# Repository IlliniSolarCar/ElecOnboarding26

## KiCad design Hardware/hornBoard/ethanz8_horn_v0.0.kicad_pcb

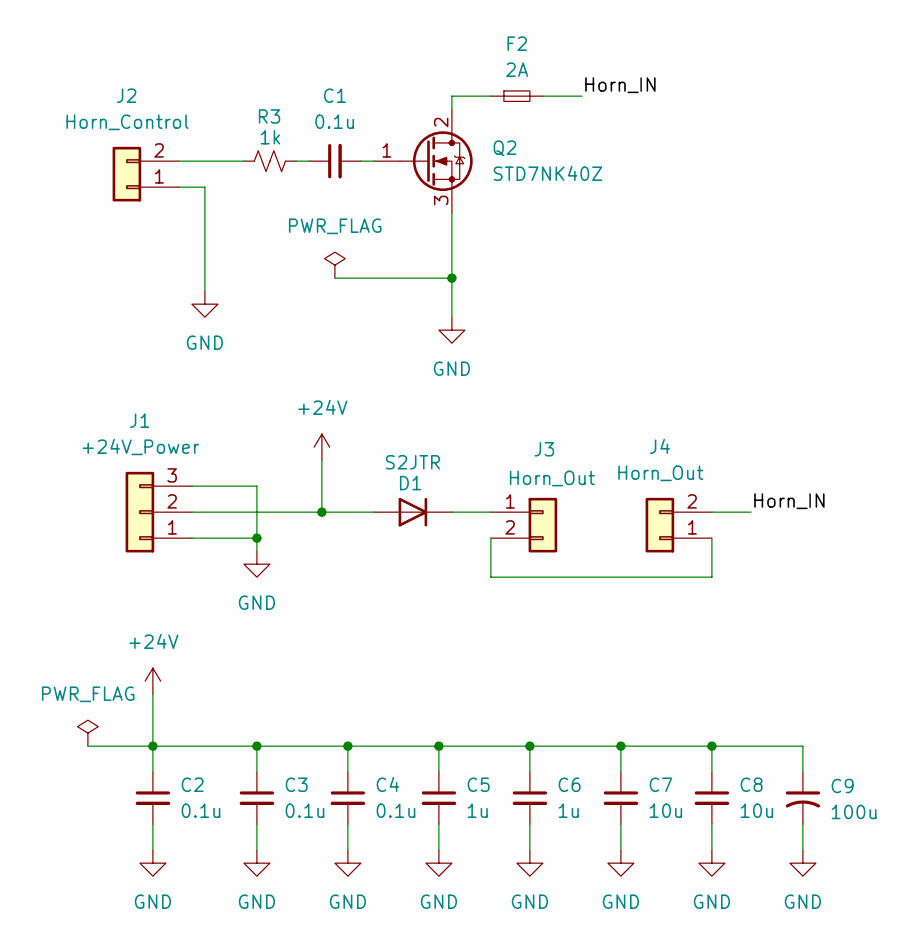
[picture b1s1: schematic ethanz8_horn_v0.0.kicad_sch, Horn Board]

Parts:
C1, C2, C3, C4: 0.1u; C_0402_1005Metric_Pad0.74x0.62mm_HandSolder
C5, C6: 1u; C_0603_1608Metric_Pad1.08x0.95mm_HandSolder
C7, C8: 10u; CP_Elec_4x5.4
C9: 100u; CP_Elec_8x10
D1: S2JTR; D_SMB
F2: 2A; Fuse_0402_1005Metric_Pad0.77x0.64mm_HandSolder
J1: +24V_Power; Molex_KK-254_AE-6410-03A_1x03_P2.54mm_Vertical
J2: Horn_Control; Molex_KK-254_AE-6410-02A_1x02_P2.54mm_Vertical
J3, J4: Horn_Out; Molex_KK-254_AE-6410-02A_1x02_P2.54mm_Vertical
Q2: STD7NK40Z; TO-252-2
R3: 1k; R_0603_1608Metric_Pad0.98x0.95mm_HandSolder

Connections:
+24V: C2.1, C3.1, C4.1, C5.1, C6.1, C7.1, C8.1, C9.1, D1.2 (A), J1.2
/Horn_IN: F2.2, J4.2
GND: C2.2, C3.2, C4.2, C5.2, C6.2, C7.2, C8.2, C9.2, J1.1, J1.3, J2.1, Q2.3 (S)
unnamed: C1.1, R3.2
unnamed: D1.1 (K), J3.1
unnamed: J2.2, R3.1
unnamed: J3.2, J4.1
unnamed: F2.1, Q2.2 (D)
unnamed: C1.2, Q2.1 (G)

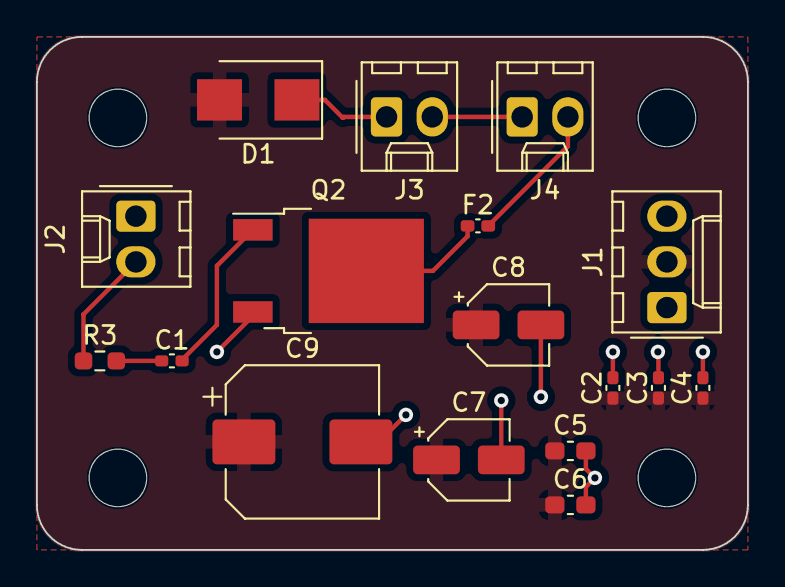
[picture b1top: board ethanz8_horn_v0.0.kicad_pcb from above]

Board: 2 copper layers, 39.5 x 28.5 mm, 17 parts (0 on the bottom side), 9 nets.

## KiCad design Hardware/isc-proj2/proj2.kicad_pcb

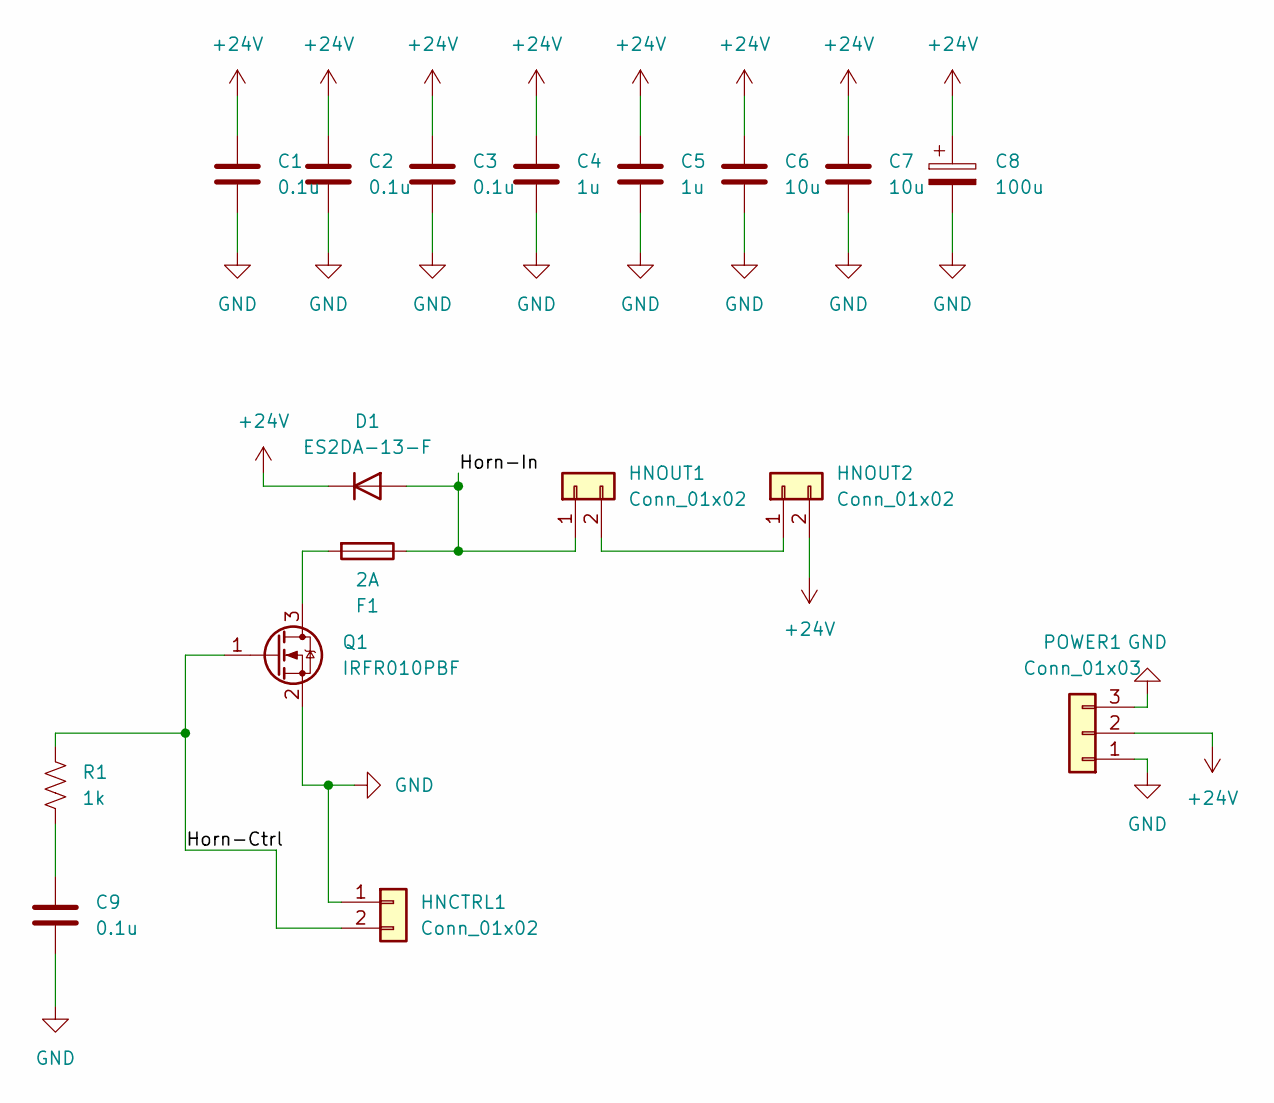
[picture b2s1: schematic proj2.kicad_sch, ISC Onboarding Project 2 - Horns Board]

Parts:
C1, C2, C3, C9: 0.1u; C_0402_1005Metric_Pad0.74x0.62mm_HandSolder
C4, C5: 1u; C_0402_1005Metric_Pad0.74x0.62mm_HandSolder
C6, C7: 10u; C_0402_1005Metric_Pad0.74x0.62mm_HandSolder
C8: 100u; C_0402_1005Metric_Pad0.74x0.62mm_HandSolder
D1: ES2DA-13-F; D_3220_8050Metric_Pad2.65x5.15mm_HandSolder
F1: 2A; Fuse_0402_1005Metric_Pad0.77x0.64mm_HandSolder
HNCTRL1: Conn_01x02; Molex_KK-254_AE-6410-02A_1x02_P2.54mm_Vertical
HNOUT1, HNOUT2: Conn_01x02; Molex_KK-254_AE-6410-02A_1x02_P2.54mm_Vertical
POWER1: Conn_01x03; Molex_KK-254_AE-6410-03A_1x03_P2.54mm_Vertical
Q1: IRFR010PBF; SOT-23
R1: 1k; R_0603_1608Metric_Pad0.98x0.95mm_HandSolder

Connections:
+24V: C1.1, C2.1, C3.1, C4.1, C5.1, C6.1, C7.1, C8.1, D1.1 (K), HNOUT2.2, POWER1.2
/Horn-Ctrl: HNCTRL1.2, Q1.1 (G), R1.1
/Horn-In: D1.2 (A), F1.1, HNOUT1.1
GND: C1.2, C2.2, C3.2, C4.2, C5.2, C6.2, C7.2, C8.2, C9.2, HNCTRL1.1, POWER1.1, POWER1.3, Q1.2 (S)
unnamed: C9.1, R1.2
unnamed: HNOUT1.2, HNOUT2.1
unnamed: F1.2, Q1.3 (D)

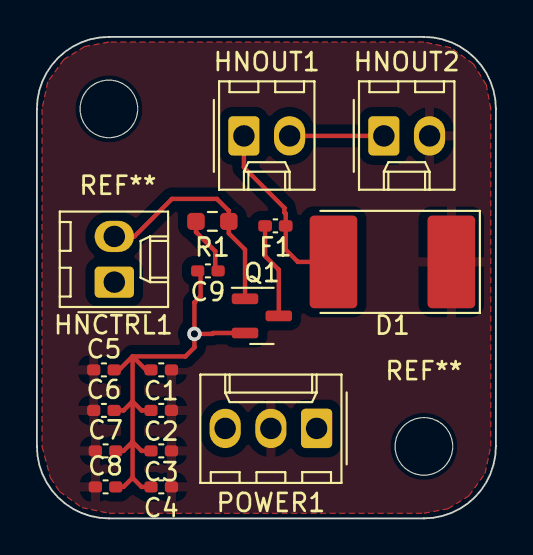
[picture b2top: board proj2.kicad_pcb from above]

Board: 2 copper layers, 25.5 x 26.8 mm, 17 parts (0 on the bottom side), 7 nets.

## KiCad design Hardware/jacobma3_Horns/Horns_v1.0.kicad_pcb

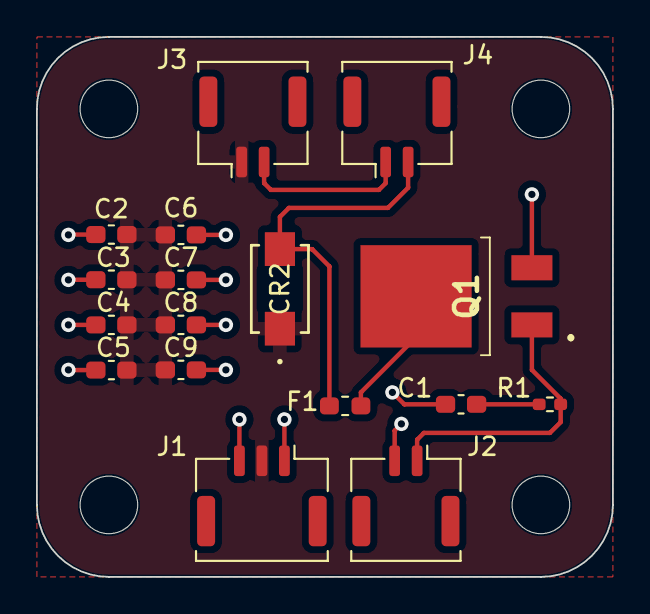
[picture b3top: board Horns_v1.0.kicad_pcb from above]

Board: 2 copper layers, 32.0 x 30.0 mm, 17 parts (0 on the bottom side), 7 nets.

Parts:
C1, C2, C3, C4: .1μF; C_0603_1608Metric_Pad1.08x0.95mm_HandSolder
C5, C6: 1μF; C_0603_1608Metric_Pad1.08x0.95mm_HandSolder
C7, C8: 10μF; C_0603_1608Metric_Pad1.08x0.95mm_HandSolder
C9: 100μF; C_0603_1608Metric_Pad1.08x0.95mm_HandSolder
CR2: ES2DA-13-F; CR_SMA_DIO
F1: 2A; Fuse_0603_1608Metric_Pad1.05x0.95mm_HandSolder
J1: Conn_01x03; Molex_CLIK-Mate_502382-0370_1x03-1MP_P1.25mm_Vertical
J2, J3, J4: Conn_01x02; Molex_CLIK-Mate_502382-0270_1x02-1MP_P1.25mm_Vertical
Q1: IRFR010PBF-BE3; SQD30N0520L_GE3
R1: 1k; R_0402_1005Metric_Pad0.72x0.64mm_HandSolder

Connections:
+24V: C2.2, C3.2, C4.2, C5.2, C6.2, C7.2, C8.2, C9.1, CR2.1, J1.2, J3.1
/HORN_CTRL: J2.1, Q1.1 (G), R1.2
/HORN_IN: CR2.2, F1.2, J4.2
GND: C1.1, C2.1, C3.1, C4.1, C5.1, C6.1, C7.1, C8.1, C9.2, J1.1, J1.3, J2.2, Q1.3 (S)
unnamed: C1.2, R1.1
unnamed: J3.2, J4.1
unnamed: F1.1, Q1.2 (D)

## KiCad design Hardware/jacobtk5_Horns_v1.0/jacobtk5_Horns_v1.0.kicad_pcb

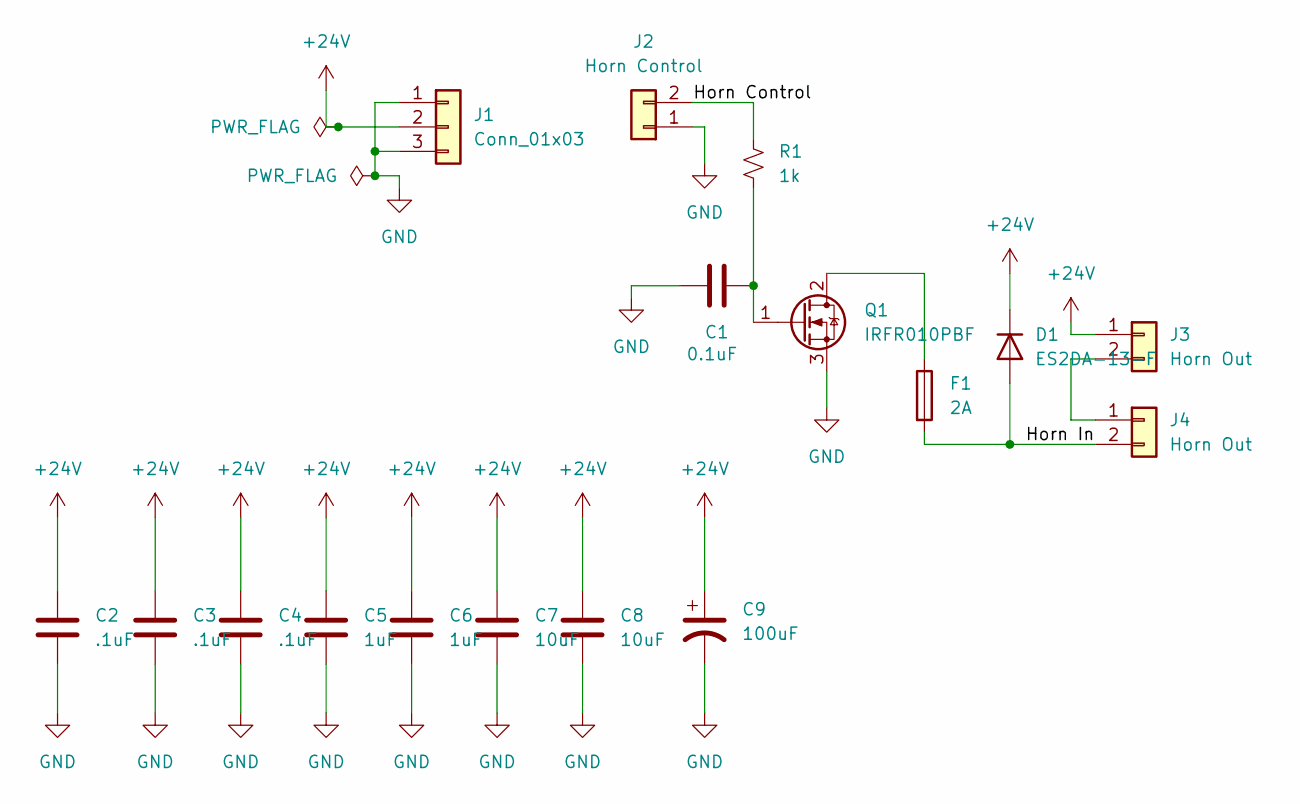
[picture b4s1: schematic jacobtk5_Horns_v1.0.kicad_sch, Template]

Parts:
C1: 0.1uF; CP_Elec_3x5.3
C2, C3, C4: .1uF; CP_Elec_3x5.3
C5, C6: 1uF; CP_Elec_3x5.3
C7, C8: 10uF; CP_Elec_3x5.3
C9: 100uF; CP_Elec_3x5.3
D1: ES2DA-13-F; D_SMB
F1: 2A; Fuse_0402_1005Metric
J1: Conn_01x03; Molex_KK-254_AE-6410-03A_1x03_P2.54mm_Vertical
J2: Horn Control; Molex_KK-254_AE-6410-02A_1x02_P2.54mm_Vertical
J3, J4: Horn Out; Molex_KK-254_AE-6410-02A_1x02_P2.54mm_Vertical
Q1: IRFR010PBF; TO-252-3_TabPin2
R1: 1k; R_0603_1608Metric_Pad0.98x0.95mm_HandSolder

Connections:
+24V: C2.1, C3.1, C4.1, C5.1, C6.1, C7.1, C8.1, C9.1, D1.1 (K), J1.2, J3.1
/Horn Control: J2.2, R1.1
/Horn In: D1.2 (A), F1.2, J4.2
GND: C1.2, C2.2, C3.2, C4.2, C5.2, C6.2, C7.2, C8.2, C9.2, J1.1, J1.3, J2.1, Q1.3 (S)
unnamed: J3.2, J4.1
unnamed: F1.1, Q1.2 (D)
unnamed: C1.1, Q1.1 (G), R1.2

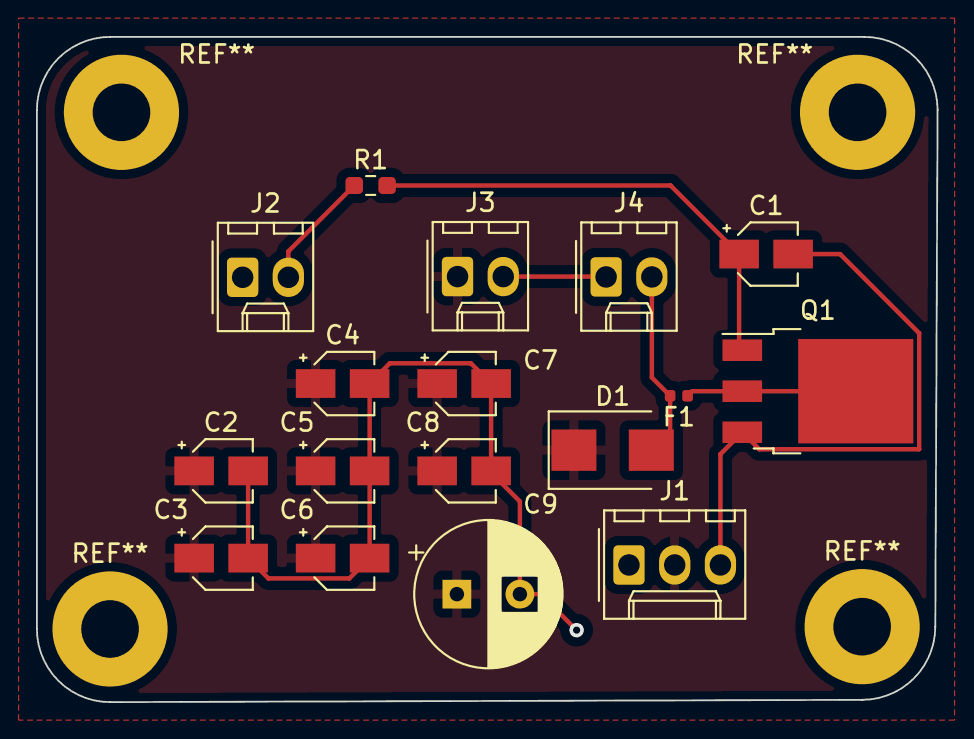
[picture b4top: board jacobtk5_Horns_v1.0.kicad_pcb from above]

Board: 2 copper layers, 50.0 x 37.0 mm, 17 parts (0 on the bottom side), 7 nets.

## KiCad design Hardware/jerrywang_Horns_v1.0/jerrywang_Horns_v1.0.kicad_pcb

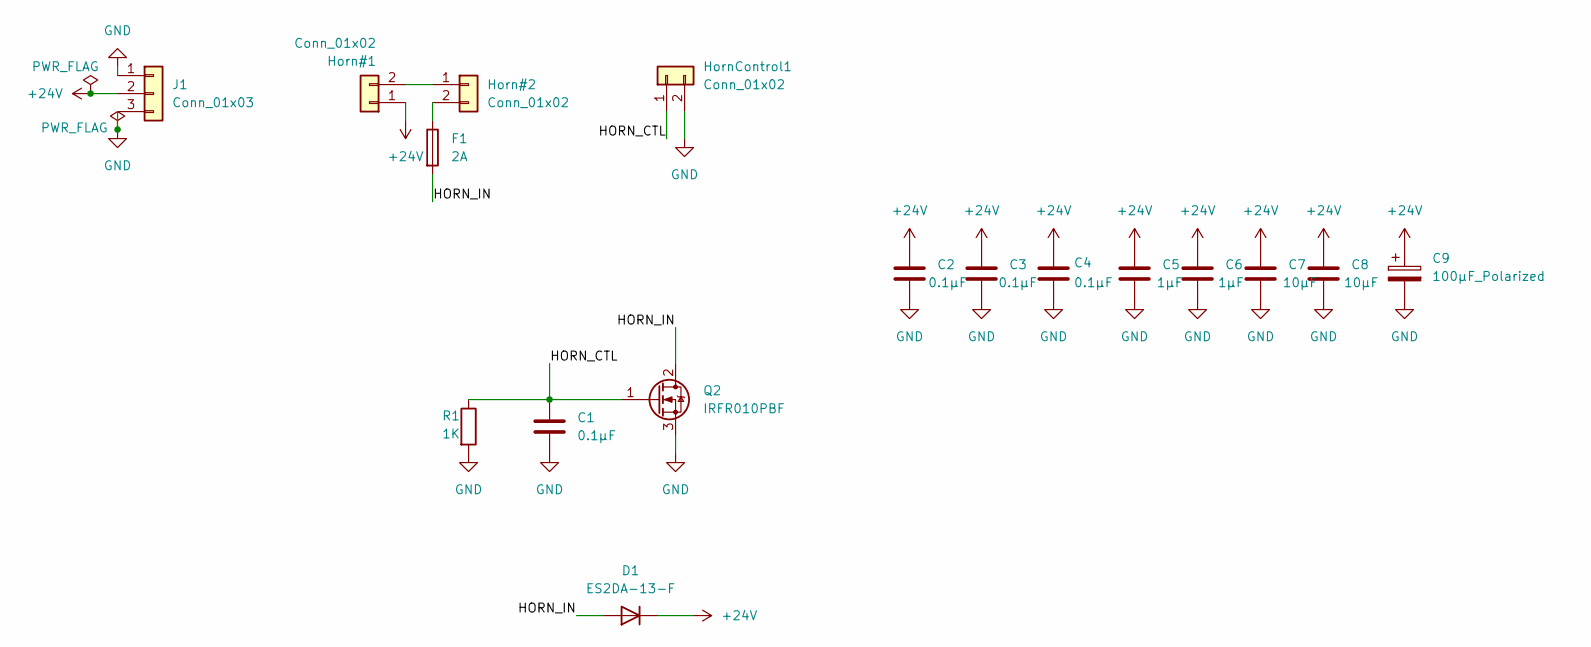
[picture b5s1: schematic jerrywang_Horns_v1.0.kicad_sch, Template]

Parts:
C1, C2, C3, C4: 0.1µF; C_1206_3216Metric
C5, C6: 1µF; C_1206_3216Metric
C7, C8: 10µF; C_1206_3216Metric
C9: 100µF_Polarized; CP_Radial_D8.0mm_P3.50mm
D1: ES2DA-13-F; D_SMA
F1: 2A; Fuse_1206_3216Metric
Horn#1, Horn#2: Conn_01x02; PinSocket_1x02_P2.54mm_Vertical
HornControl1: Conn_01x02; PinSocket_1x02_P2.54mm_Vertical
J1: Conn_01x03; PinSocket_1x03_P2.54mm_Vertical
Q2: IRFR010PBF; TO-252-2
R1: 1K; R_1206_3216Metric

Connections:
+24V: C2.1, C3.1, C4.1, C5.1, C6.1, C7.1, C8.1, C9.1, D1.1 (K), Horn#1.1, J1.2
/HORN_CTL: C1.1, HornControl1.1, Q2.1 (G), R1.1
/HORN_IN: D1.2 (A), F1.2, Q2.2 (D)
GND: C1.2, C2.2, C3.2, C4.2, C5.2, C6.2, C7.2, C8.2, C9.2, HornControl1.2, J1.1, J1.3, Q2.3 (S), R1.2
unnamed: Horn#1.2, Horn#2.1
unnamed: F1.1, Horn#2.2

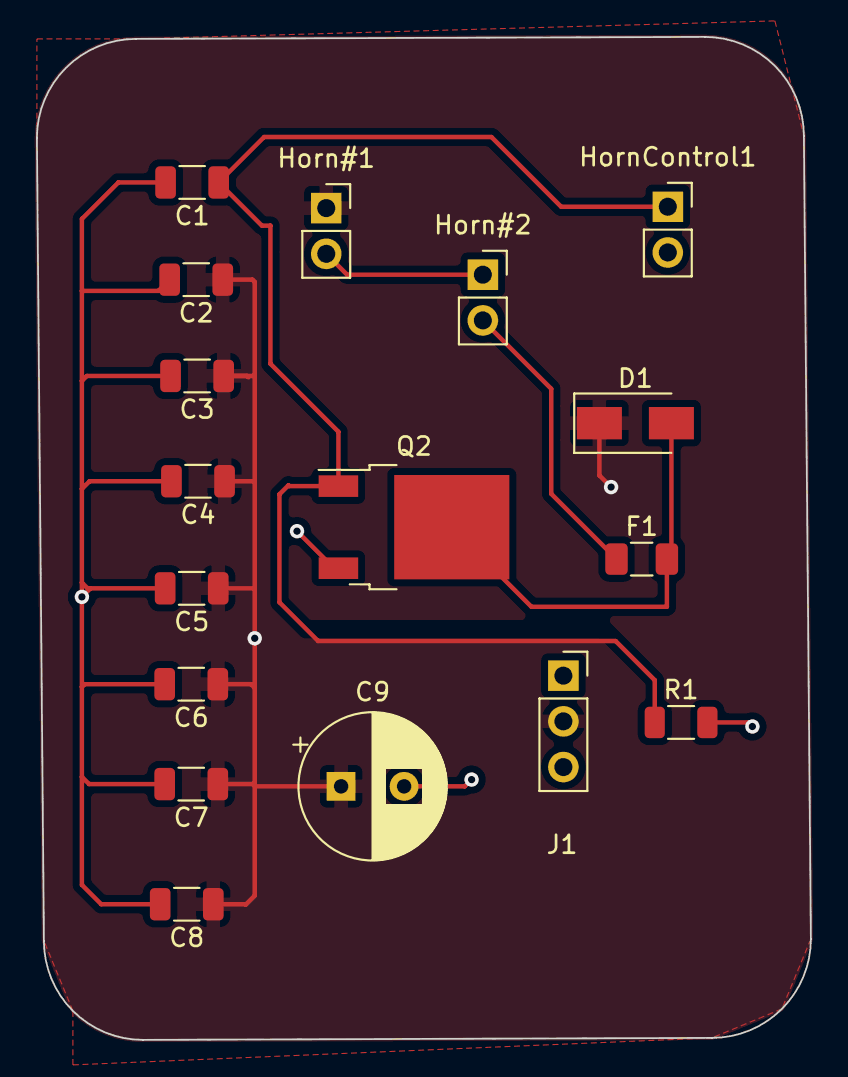
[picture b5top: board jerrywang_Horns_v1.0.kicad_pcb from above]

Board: 2 copper layers, 43.0 x 55.7 mm, 17 parts (0 on the bottom side), 6 nets.

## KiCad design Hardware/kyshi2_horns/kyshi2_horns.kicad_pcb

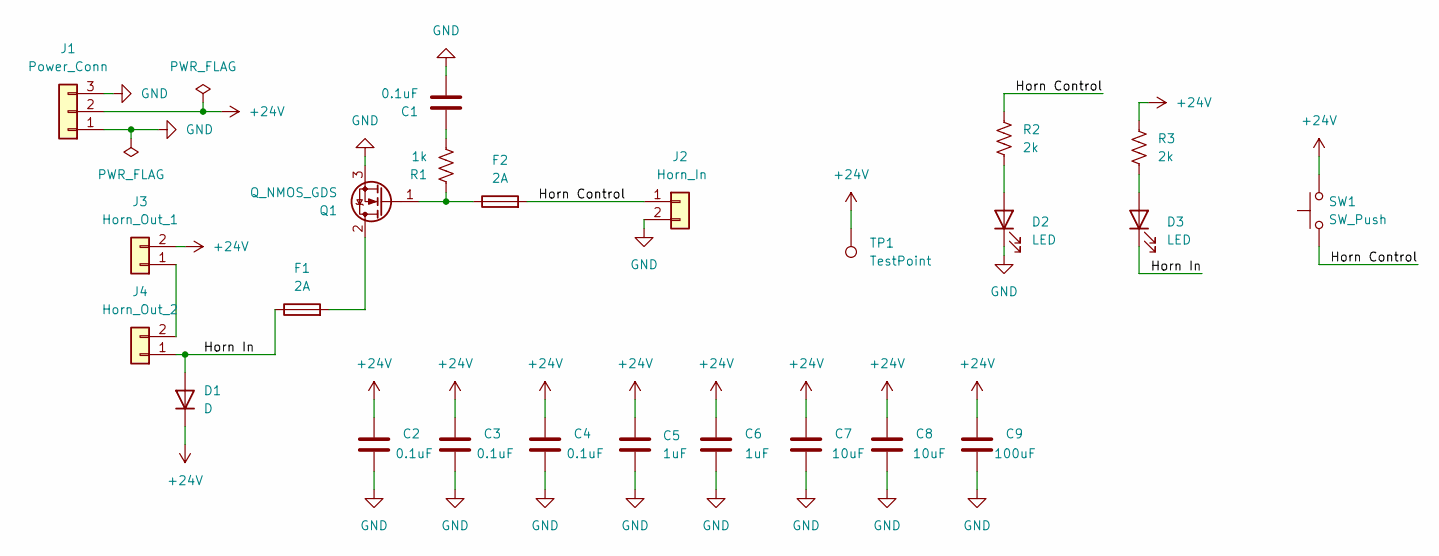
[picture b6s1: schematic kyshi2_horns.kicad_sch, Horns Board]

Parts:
C1, C2, C3, C4: 0.1uF; C_0201_0603Metric_Pad0.64x0.40mm_HandSolder
C5, C6: 1uF; C_0201_0603Metric_Pad0.64x0.40mm_HandSolder
C7, C8: 10uF; C_0201_0603Metric_Pad0.64x0.40mm_HandSolder
C9: 100uF; C_0201_0603Metric_Pad0.64x0.40mm_HandSolder
D1: D; D_SMA
D2, D3: LED; LED_0603_Symbol_on_F.SilkS
F1, F2: 2A; Fuse_1206_3216Metric
J1: Power_Conn; Molex_KK-254_AE-6410-03A_1x03_P2.54mm_Vertical
J2: Horn_In; Molex_KK-254_AE-6410-02A_1x02_P2.54mm_Vertical
J3: Horn_Out_1; Molex_KK-254_AE-6410-02A_1x02_P2.54mm_Vertical
J4: Horn_Out_2; Molex_KK-254_AE-6410-02A_1x02_P2.54mm_Vertical
Q1: Q_NMOS_GDS; TO-252-3_TabPin2; MPN IRFR010PBF
R1: 1k; R_0603_1608Metric_Pad0.98x0.95mm_HandSolder
R2, R3: 2k; R_0603_1608Metric_Pad0.98x0.95mm_HandSolder
SW1: SW_Push; SW_DIP_SPSTx01_Slide_6.7x4.1mm_W8.61mm_P2.54mm_LowProfile
TP1: TestPoint; TestPoint_Keystone_5019_Minature

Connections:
+24V: C2.2, C3.2, C4.2, C5.2, C6.2, C7.2, C8.2, C9.2, D1.1 (K), J1.2, J3.2, R3.2, SW1.2, TP1.1
/Horn Control: F2.2, J2.1, R2.2, SW1.1
/Horn In: D1.2 (A), D3.1 (K), F1.1, J4.1
GND: C1.2, C2.1, C3.1, C4.1, C5.1, C6.1, C7.1, C8.1, C9.1, D2.1 (K), J1.1, J1.3, J2.2, Q1.3 (S)
unnamed: C1.1, R1.2
unnamed: D2.2 (A), R2.1
unnamed: D3.2 (A), R3.1
unnamed: J3.1, J4.2
unnamed: F1.2, Q1.2 (D)
unnamed: F2.1, Q1.1 (G), R1.1

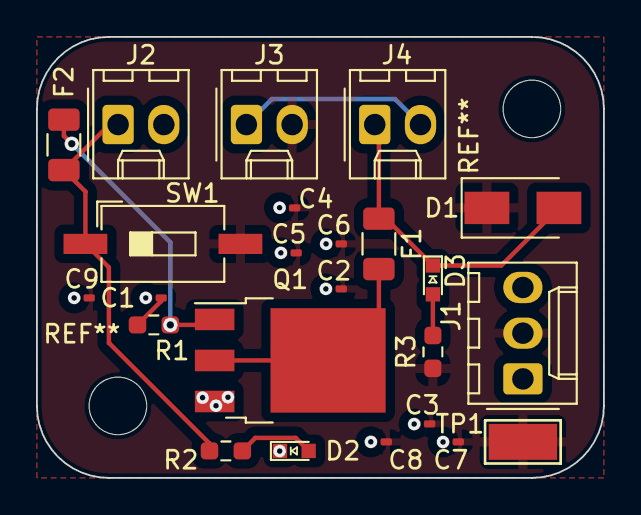
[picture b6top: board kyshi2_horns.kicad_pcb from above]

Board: 2 copper layers, 31.5 x 24.5 mm, 24 parts (0 on the bottom side), 10 nets.

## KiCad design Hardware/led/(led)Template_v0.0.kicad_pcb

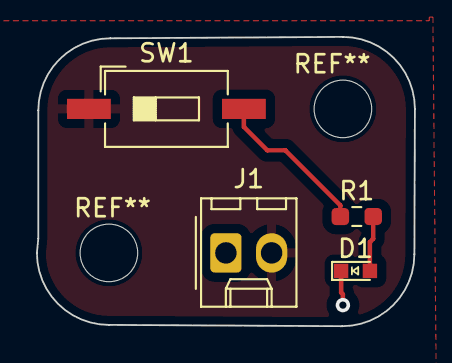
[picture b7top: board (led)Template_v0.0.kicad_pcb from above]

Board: 2 copper layers, 21.0 x 16.1 mm, 4 parts (0 on the bottom side), 4 nets.

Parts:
D1: LED_BLUE; LED_0603_Symbol_on_F.SilkS
J1: Conn_01x02; Molex_KK-254_AE-6410-02A_1x02_P2.54mm_Vertical
R1: 105; R_0603_1608Metric_Pad0.98x0.95mm_HandSolder
SW1: SW_Push; SW_DIP_SPSTx01_Slide_6.7x4.1mm_W8.61mm_P2.54mm_LowProfile

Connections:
+3V3: J1.2, SW1.1
GND: D1.1 (K), J1.1
unnamed: D1.2 (A), R1.2
unnamed: R1.1, SW1.2
